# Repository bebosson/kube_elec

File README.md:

# Le Kube (School Electronic Project) 
Implementation of an IoT solution for growing plants.\
Development of the Bill of Materials (BOM), Specification Document, and PCB Fabrication. \
Electrical schematics, circuit design, and component soldering. \
Firmware development in C for Atmega328p and ESP328p microcontrollers, along with an Adafruit screen. \
Implementation of UART, SPI, and I2C protocols, AT command usage, EEPROM memory handling, timers, and interrupts. \
LAMP stack setup on Raspberry Pi with JavaScript and MySQL solutions. \

\
The data collected by the sensors are sent via wifi and accessible online, as well as on the Oled screen.
Variables monitored by the captors:
* `soil moisture
* `light
* `temperature
A water pump is connected to an optocoupler to automate the watering.

## Block diagram

## Electric diagram

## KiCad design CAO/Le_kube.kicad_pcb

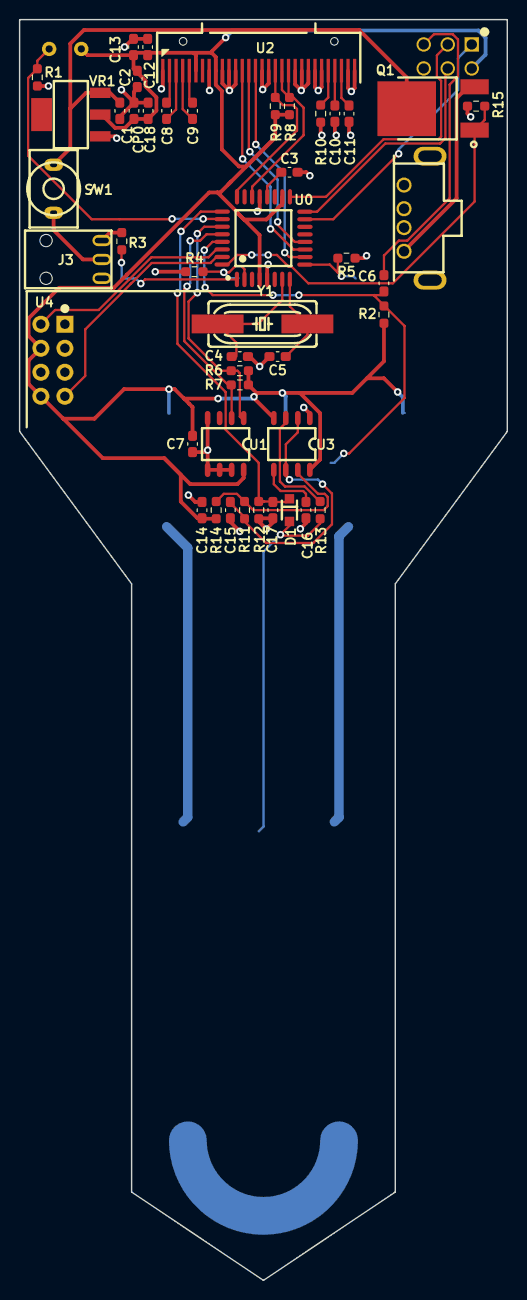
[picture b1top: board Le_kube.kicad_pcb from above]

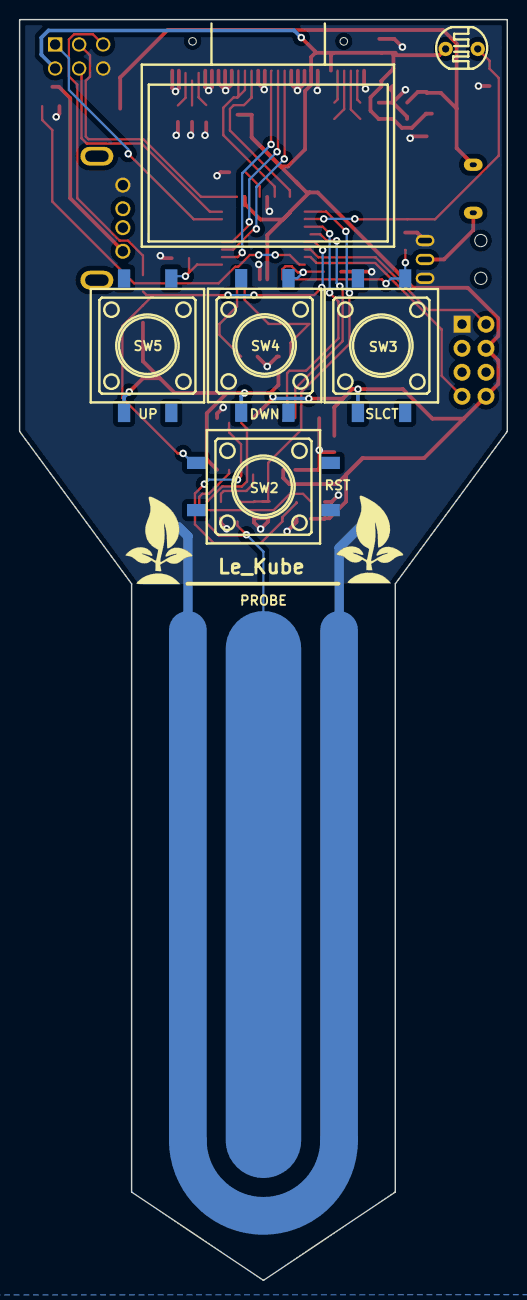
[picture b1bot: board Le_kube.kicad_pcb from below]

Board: 2 copper layers, 51.6 x 133.4 mm, 53 parts (6 on the bottom side), 40 nets.

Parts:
C1, C3, C6, C7, C14, C18: 100nF; C_0603_1608Metric_Pad1.08x0.95mm_HandSolder
C2: 10µF; C_0603_1608Metric_Pad1.08x0.95mm_HandSolder
C4, C5: 30pF; C_0603_1608Metric_Pad1.08x0.95mm_HandSolder
C8, C9, C12, C13, C17: 1µF; C_0603_1608Metric_Pad1.08x0.95mm_HandSolder
C10: 4.7µF; C_0603_1608Metric_Pad1.08x0.95mm_HandSolder
C11: 2.2µF; C_0603_1608Metric_Pad1.08x0.95mm_HandSolder
C15: 470pF; C_0603_1608Metric_Pad1.08x0.95mm_HandSolder
C16: 10nF; C_0603_1608Metric_Pad1.08x0.95mm_HandSolder
C19: PROBE
CP0: 10µF; C_0603_1608Metric_Pad1.08x0.95mm_HandSolder
D1: D; SOD-323_L1.8-W1.3-LS2.5-RD
J1: Conn_01x06_Male; AVR-ISP(IDC-TH_6P-P2.54_C11214)
J2: USB_A; USB-A-TH_USB-302-T
J3: Barrel_Jack_Switch; PORT-JACK(DC-IN-TH_DC-003-2A-1.3)
LDR1: LDR; LDR(RES-TH_L5.1-W4.3-P3.40-D0.5)
Q1: IRLB8721PBF; MOSFET(DPAK_L6.5-W6.0-P2.29-LS9.9-BR)
R1, R2, R3, R4, R5, R6, R7, R13, R15: 10K; R_0603_1608Metric_Pad0.98x0.95mm_HandSolder
R8, R9: 4.7K; R_0603_1608Metric_Pad0.98x0.95mm_HandSolder
R10: 910K; R_0603_1608Metric_Pad0.98x0.95mm_HandSolder
R11: 1.6K; R_0603_1608Metric_Pad0.98x0.95mm_HandSolder
R12: 1M; R_0603_1608Metric_Pad0.98x0.95mm_HandSolder
R14: 330R; R_0603_1608Metric_Pad0.98x0.95mm_HandSolder
SW1: I/O; SW-TH_L8.0-W5.11-P5.08_TP11SH8CQE
SW2: RST; KEY-SMD_4P-L12.0-W12.0-P5.00-LS15.2
SW3, SW4, SW5: SW_Push; KEY-SMD_4P-L12.0-W12.0-P5.00-LS15.2
U0: ATmega328PB-AU; ATMEGA328PB-AU(TQFP-32_L7.0-W7.0-P0.80-LS9.0-BL)
U1: LM75A; TEMP_SENSOR(SOIC-8_L5.0-W4.0-P1.27-LS6.0-BL)
U2: 128x64_OLED; OLED-0.96-12864
U3: TLC555CDR; TLC555(SOIC-8_L5.0-W4.0-P1.27-LS6.0-BL)
U4: ESP8266-01_ESP-01; ESP-01S(WIFIM-TH_8P-L24.7-W14.4-P2.54)
VR1: LD1117; LD1117(SOT-223_L6.7-W3.5-P2.30-BR)
Y1: Crystal; Crystal(HC-49S_L11.4-W4.8)

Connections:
+3V3: C2.1, C7.2, C12.1, C13.1, C14.2, C18.1, CP0.1, J1.2, LDR1.2, R2.1, R6.1, R7.2, R8.2, R9.2, R14.2, SW3.4, SW4.4, SW5.4, U0.4, U0.18, U1.8, U2.6, U2.9, U3.4, U3.8, U4.6, U4.8, VR1.2
+5V: J3.2, SW1.1
/ESP_RX: U0.31, U4.4
/ESP_TX: U0.30, U4.5
/HUM: C17.2, D1.1, R12.2, U0.25
/ISP_MISO: J1.1, U0.15
/ISP_MOSI: J1.4, U0.16
/ISP_SCK: J1.3, U0.17
/SCL: R7.1, U0.28, U1.2
/SCREEN_MISO: R8.1, U0.22, U2.19, U2.20
/SCREEN_MOSI: U0.10, U2.15
/SCREEN_RST: U0.12, U2.14
/SCREEN_SCK: R9.1, U0.24, U2.18
/SCREEN_SS: U0.11, U2.13
/SDA: R6.2, U0.27, U1.1
/connecteur_isp/RST: C6.1, J1.5
GND: C1.1, C2.2, C3.2, C4.1, C5.1, C7.1, C10.1, C11.1, C12.2, C13.2, C14.1, C15.1, C16.2, C17.1, C18.2, C19.1, CP0.2, J1.6, J2.4, J3.1, J3.3, R1.1, R3.1, R4.1, R5.1, R10.2, R12.1, R15.1, SW2.4, U0.5, U0.21, U1.4, U1.5, U1.6, U1.7, U2.1, U2.8, U2.10, U2.11, U2.12, U2.16, U2.17, U2.21, U2.22, U2.23, U2.24, U2.25, U2.29, U2.30, U3.1, U4.1, VR1.1
unnamed: C1.2, Q1.4, SW1.2, VR1.3
unnamed: C3.1, U0.20
unnamed: C4.2, U0.7, Y1.1
unnamed: C5.2, U0.8, Y1.2
unnamed: C6.2, R2.2, SW2.1, U0.29
unnamed: C8.1, U2.2
unnamed: C8.2, U2.3
unnamed: C9.1, U2.4
unnamed: C9.2, U2.5
unnamed: C10.2, U2.27
unnamed: C11.2, U2.28
unnamed: C15.2, R11.1, U3.2, U3.6
unnamed: C16.1, U3.5
unnamed: C19.2, D1.2, R13.1
unnamed: J2.1, Q1.3
unnamed: LDR1.1, R1.2, U0.26
unnamed: Q1.1, R15.2, U0.32
unnamed: R3.2, SW3.1, U0.1
unnamed: R4.2, SW4.1, U0.2
unnamed: R5.2, SW5.1, U0.9
unnamed: R10.1, U2.26
unnamed: R11.2, R14.1, U3.7
unnamed: R13.2, U3.3
